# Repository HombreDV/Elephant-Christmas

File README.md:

# Elephant-Christmas
Christmas gift 

The elephant will be configured to link with other elephants to notify user that they are thinking of them.

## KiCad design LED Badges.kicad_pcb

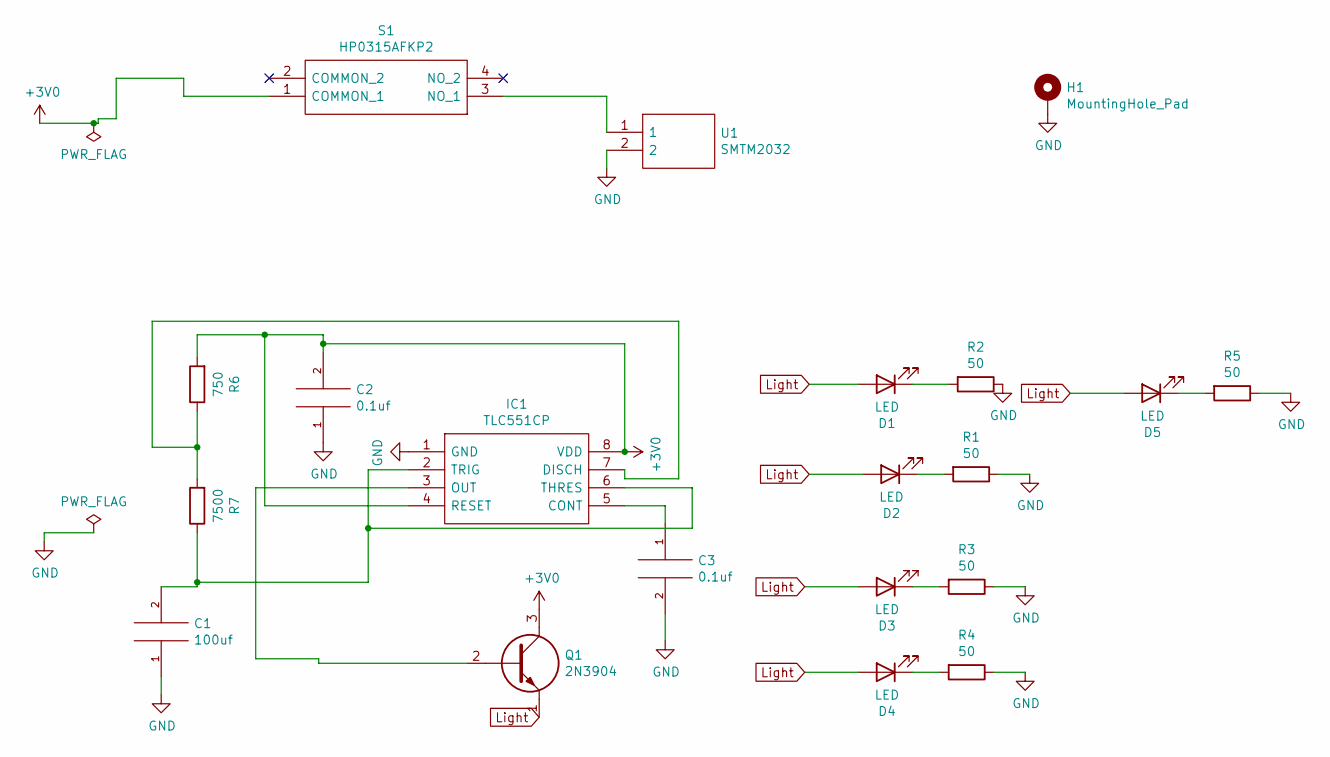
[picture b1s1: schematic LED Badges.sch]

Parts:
C1: 100uf; CP_Radial_D8.0mm_P3.50mm
C2, C3: 0.1uf; C_Disc_D5.1mm_W3.2mm_P5.00mm
D1, D2, D3, D4, D5: LED; LED_1206_3216Metric_Pad1.42x1.75mm_HandSolder
H1: MountingHole_Pad; MountingHole_2.2mm_M2_ISO14580_Pad_TopBottom
IC1: TLC551CP; DIP794W53P254L959H508Q8N; Mouser Part Number 595-TLC551CP
Q1: 2N3904; TO254P508X877-3; Mouser Part Number 512-2N3904
R1, R2, R3, R4, R5: 50; R_Axial_DIN0207_L6.3mm_D2.5mm_P10.16mm_Horizontal
R6: 750; R_Axial_DIN0207_L6.3mm_D2.5mm_P10.16mm_Horizontal
R7: 7500; R_Axial_DIN0207_L6.3mm_D2.5mm_P10.16mm_Horizontal
S1: HP0315AFKP2; Mouser Part Number 633-HP0315AFKP2
U1: SMTM2032; 1061; Manufacturer_Part_Number SMTM2032; Mouser Part Number 614-SMTM2032

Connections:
+3V0: C2.2, IC1.4 (RESET), IC1.8 (VDD), Q1.3, R6.2, S1.1 (COMMON_1)
GND: C1.1, C2.1, C3.2, H1.1, IC1.1 (GND), R1.1, R2.1, R3.1, R4.1, R5.1, U1.2
Light: D1.2 (A), D2.2 (A), D3.2 (A), D4.2 (A), D5.2 (A), Q1.1
unnamed: C1.2, IC1.2 (TRIG), IC1.6 (THRES), R7.1
unnamed: C3.1, IC1.5 (CONT)
unnamed: D1.1 (K), R2.2
unnamed: D2.1 (K), R1.2
unnamed: D3.1 (K), R3.2
unnamed: D4.1 (K), R4.2
unnamed: D5.1 (K), R5.2
unnamed: IC1.3 (OUT), Q1.2
unnamed: IC1.7 (DISCH), R6.1, R7.2
unnamed: S1.3 (NO_1), U1.1

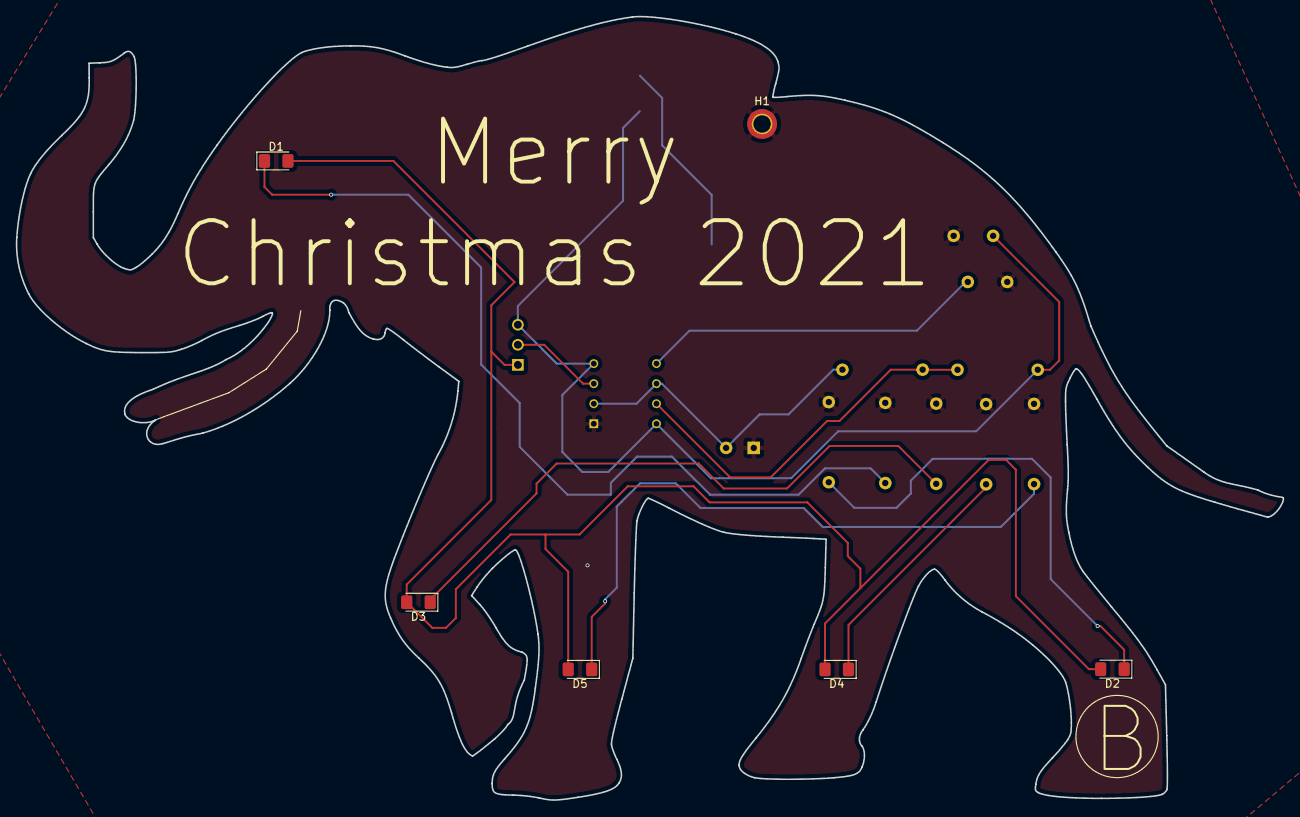
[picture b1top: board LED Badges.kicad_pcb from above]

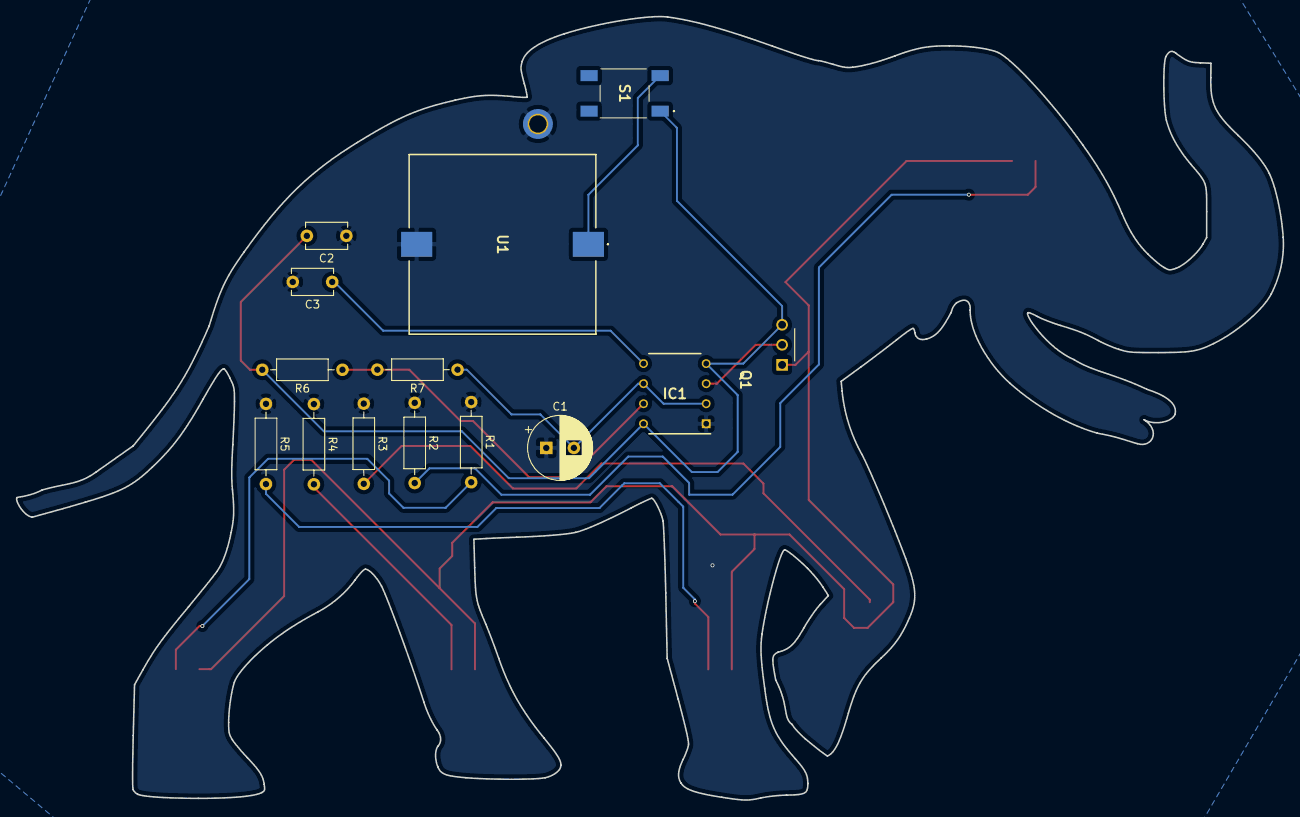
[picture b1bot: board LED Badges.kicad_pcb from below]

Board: 2 copper layers, 160.5 x 99.3 mm, 20 parts (14 on the bottom side), 13 nets.

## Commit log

2022-01-19 Changes to the origin
2022-01-19 Looking to change Read me
